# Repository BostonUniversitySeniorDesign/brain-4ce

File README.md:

<div style="text-align: center;">

# **Brain-4ce** - An EEG-based Brain-Computer Interface

</div>

<p align="center">
    
    <br>
    <em>Where thoughts become motion.</em>
</p>
<h2 style="text-decoration: underline; text-align: center">Designed by BU ECE 2023 Senior Design Capstone Team 4</h2>
<p align="center">
    
    <br>
    <em>From left to right: Brendan Shortall, Mitchell Gilmore, Dayanna De La Torres, Jonathan Mikalov, Alexander Johnson</em>
</p>
<br>

# Table of Contents
- [**Brain-4ce** - An EEG-based Brain-Computer Interface](#brain-4ce---an-eeg-based-brain-computer-interface)
- [Table of Contents](#table-of-contents)
- [Abstract](#abstract)
- [Getting Started](#getting-started)
- [Current State of the Project](#current-state-of-the-project)
- [Lessons Learned](#lessons-learned)
- [Bug Fixes](#bug-fixes)

<br>

# Abstract
The ability to manipulate objects using only your mind is no longer a far-fetched idea. While It may sound like something out of science fiction, our team has turned this into a reality. We have created a headset that utilizes electroencephalogram (EEG) technology to quickly and accurately record a user's neural activity. Our state-of-the-art deep learning algorithm then decodes these signals into predefined motor-imagery tasks.

This breakthrough technology is integrated with a computer game that provides the user with an environment to navigate using their mind. With the Brain-4ce (pronounced "Brain Force") headset, users can perform four different actions: rotating clockwise, rotating counterclockwise, moving forward, and moving backward. Each action corresponds to a physical motion that the user imagines themselves doing.

Our team was inspired to develop this project by our aspiration to bridge the digital divide for those who are physically disabled. With the Brain-4ce headset, users will be able to operate a computer, a wheelchair, and virtually anything else using nothing but their thoughts! The possibilities are endless, and we are excited to see what the future holds.
<br></br>

# Getting Started
- Please refer to our [Hardware Setup Guide](./hardware/README_HARDWARE.md) for instructions on setting up the hardware.
- Please refer to our [Software Setup Guide](./mainmenu/README_SOFTWARE.md) for instructions on setting up the software.
<br></br>

# Current State of the Project
As it currently stands, our project has three major components:
1. A working [EEG data capture headset](./hardware/electrical/cyton%20wired/) that interfaces with a [Python application](./GUI/) to monitor and record brain activity in real time.
2. A [convolutional neural network machine learning algorithm](./Physionet%20Dataloader/), trained on the recorded brain activity, for classifying motor-imagery tasks observed from a user wearing the headset.
3. [2D](./2D%20Game/) and [3D](./Virtual%20Environment/) video games developed in Python to demonstrate the efficacy of the neural network's brain activity classification.

The software communicates in real time using socket programming techniques to achieve parallelism and multithreading.
<br></br>

# Lessons Learned
- Developing on Apple Silicon, and ARM-based processors in general, is tricky for this project. Certain libraries, such as the [ChipKIT Core library](https://chipkit.net/wiki/index.php?title=ChipKIT_core) for compiling firmware onto the microcontroller, lack proper support for ARM architecture. We recommend performing all software development on an x64-based Windows machine. Some development is possible on Intel-based macOS and Linux, but it will probably save you a lot of headache to stick to Windows if possible.
- The microcontroller appears to have USB functionality built-in, which might make the USB to UART conversion unnecessary. This may be something to examine in [the documentation](https://ww1.microchip.com/downloads/en/DeviceDoc/PIC32MX1XX2XX%20283644-PIN_Datasheet_DS60001168L.pdf) during a future continuation of this project.
- The ADS1299 chip from Texas Instruments remains [difficult to obtain](https://www.findchips.com/search/ADS1299) as of Q2 2023 due to the ongoing chip shortage. We tried using the ADS1296 chip in its place, but this was unsuccessful because of differing startup and common-mode rejection configurations between the chips.
- If future boards are manufactured, it may be worth considering [paying for them to be machine-assembled](https://jlcpcb.com/parts). Assembling the boards by hand takes a long time and requires a substantial amount of electrical rules checking to ensure no shorts or incontinuity between components.
- Obtaining good skin contact for all electrodes is crucial to ensure proper reading of brain activity.
- The [OpenBCI Forum](https://openbci.com/forum/index.php?p=/discussions) is a great place to turn to for help troubleshooting. As is [their documentation](https://docs.openbci.com).
<br></br>

# Bug Fixes
- [Incorrect start byte configuration](https://github.com/atjohnson/brain-4ce-old/issues/10) - fixes an issue where the data stream is incorrectly formatted because the obsolete RFduino did some packet changing which no longer happens due to our wired USB connection.
- [Enable OpenBCI GUI to work with USB to UART controller](https://github.com/atjohnson/brain-4ce-old/issues/11) - fixes an issue where OpenBCI's GUI is unable to detect the Cyton board due to an ID mismatch with the USB to UART bridge IC.
- [Set up chipKIT Core library to work on local machine](https://github.com/atjohnson/brain-4ce-old/issues/12) - fixes an issue where Arduino IDE is unable to compile the firmware because it cannot locate the PIC32 compiler applications.
- [RXT and TXT LEDs not flashing](https://github.com/BostonUniversitySeniorDesign/brain-4ce/issues/4) - fixes an issue where the RXT and TXT LEDs on the board indicating data transmission over UART do not flash because the USB to UART bridge's firmware is configured improperly.

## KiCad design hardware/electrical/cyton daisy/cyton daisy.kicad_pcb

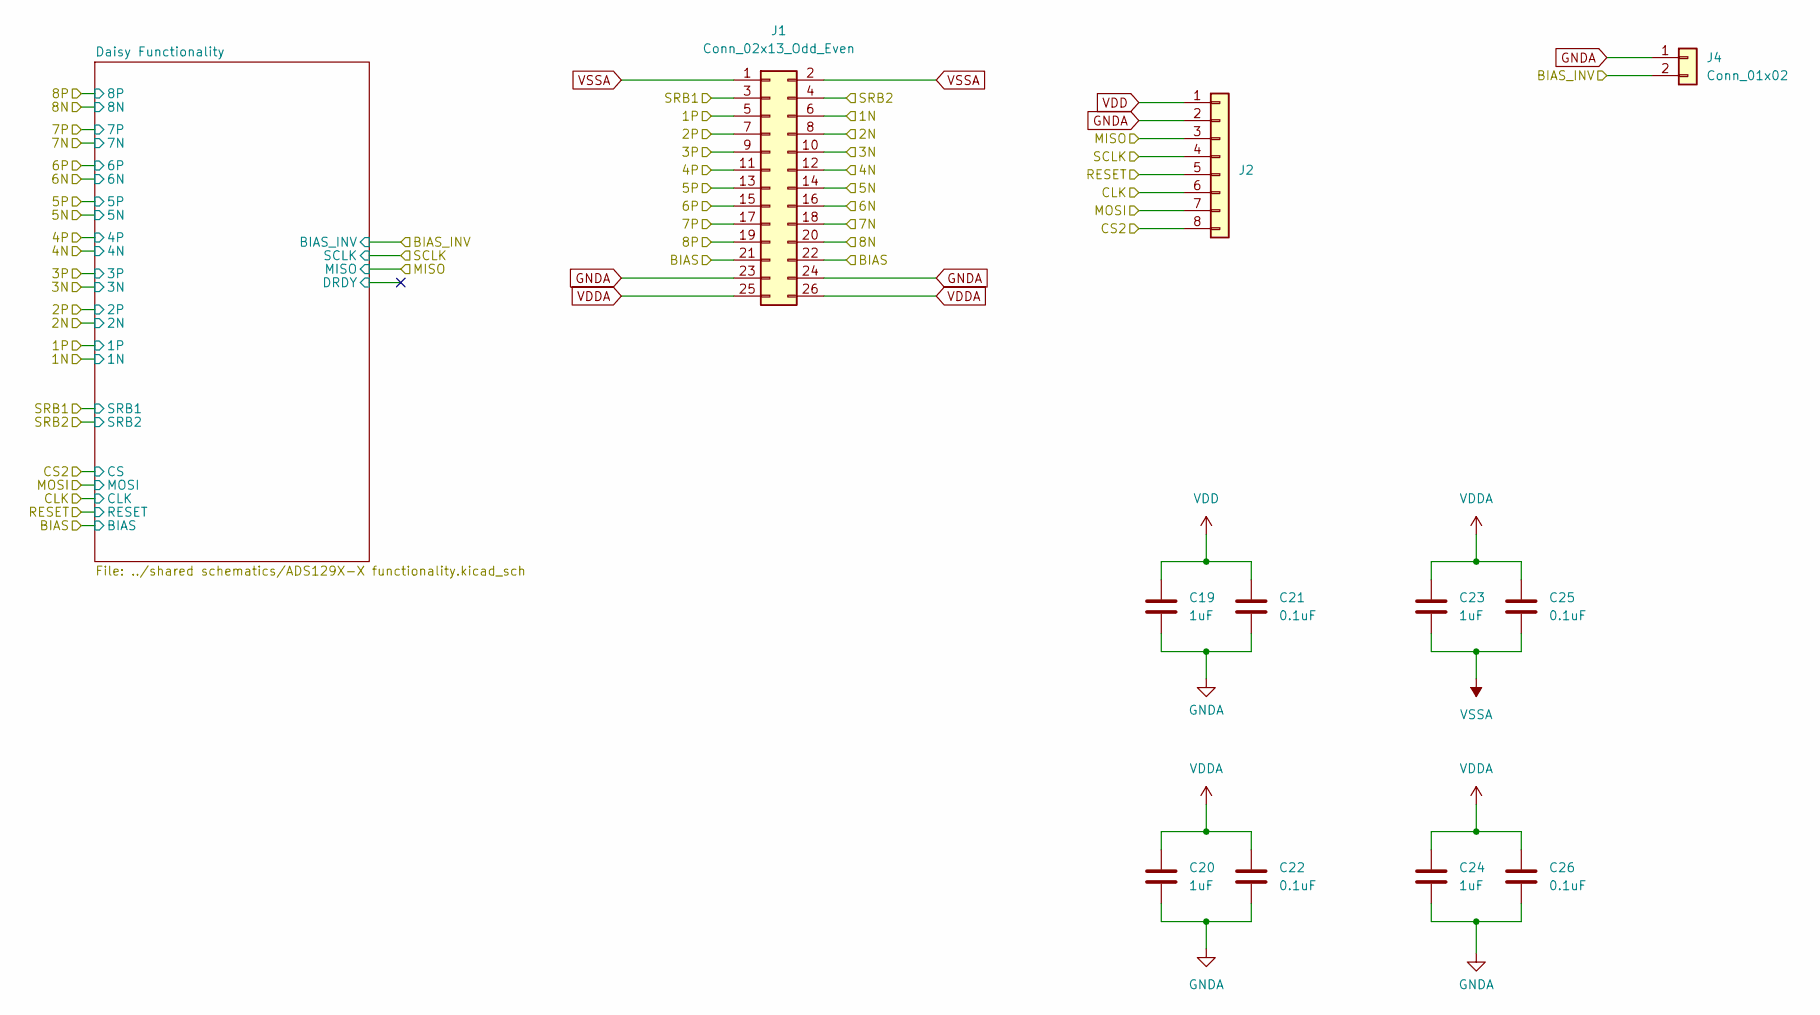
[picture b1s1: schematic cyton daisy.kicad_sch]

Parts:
C19, C20, C23, C24: 1uF; C_0402_1005Metric
C21, C22, C25, C26: 0.1uF; C_0402_1005Metric
J1: Conn_02x13_Odd_Even; PinHeader_2x13_P2.54mm_Horizontal
J2: Conn_01x08; PinSocket_1x08_P2.54mm_Vertical
J4: Conn_01x02; PinSocket_1x02_P2.54mm_Vertical

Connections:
/1N: J1.6; also elsewhere on the board
/1P: J1.5; also elsewhere on the board
/2N: J1.8; also elsewhere on the board
/2P: J1.7; also elsewhere on the board
/3N: J1.10; also elsewhere on the board
/3P: J1.9; also elsewhere on the board
/4N: J1.12; also elsewhere on the board
/4P: J1.11; also elsewhere on the board
/5N: J1.14; also elsewhere on the board
/5P: J1.13; also elsewhere on the board
/6N: J1.16; also elsewhere on the board
/6P: J1.15; also elsewhere on the board
/7N: J1.18; also elsewhere on the board
/7P: J1.17; also elsewhere on the board
/8N: J1.20; also elsewhere on the board
/8P: J1.19; also elsewhere on the board
/BIAS: J1.21, J1.22; also elsewhere on the board
/BIAS_INV: J4.2; also elsewhere on the board
/CLK: J2.6; also elsewhere on the board
/CS2: J2.8; also elsewhere on the board
/MISO: J2.3; also elsewhere on the board
/MOSI: J2.7; also elsewhere on the board
/RESET: J2.5; also elsewhere on the board
/SCLK: J2.4; also elsewhere on the board
/SRB1: J1.3; also elsewhere on the board
/SRB2: J1.4; also elsewhere on the board
GNDA: C19.2, C20.2, C21.2, C22.2, C24.2, C26.2, J1.23, J1.24, J2.2, J4.1; also elsewhere on the board
VDD: C19.1, C21.1, J2.1; also elsewhere on the board
VDDA: C20.1, C22.1, C23.1, C24.1, C25.1, C26.1, J1.25, J1.26; also elsewhere on the board
VSSA: C23.2, C25.2, J1.1, J1.2; also elsewhere on the board

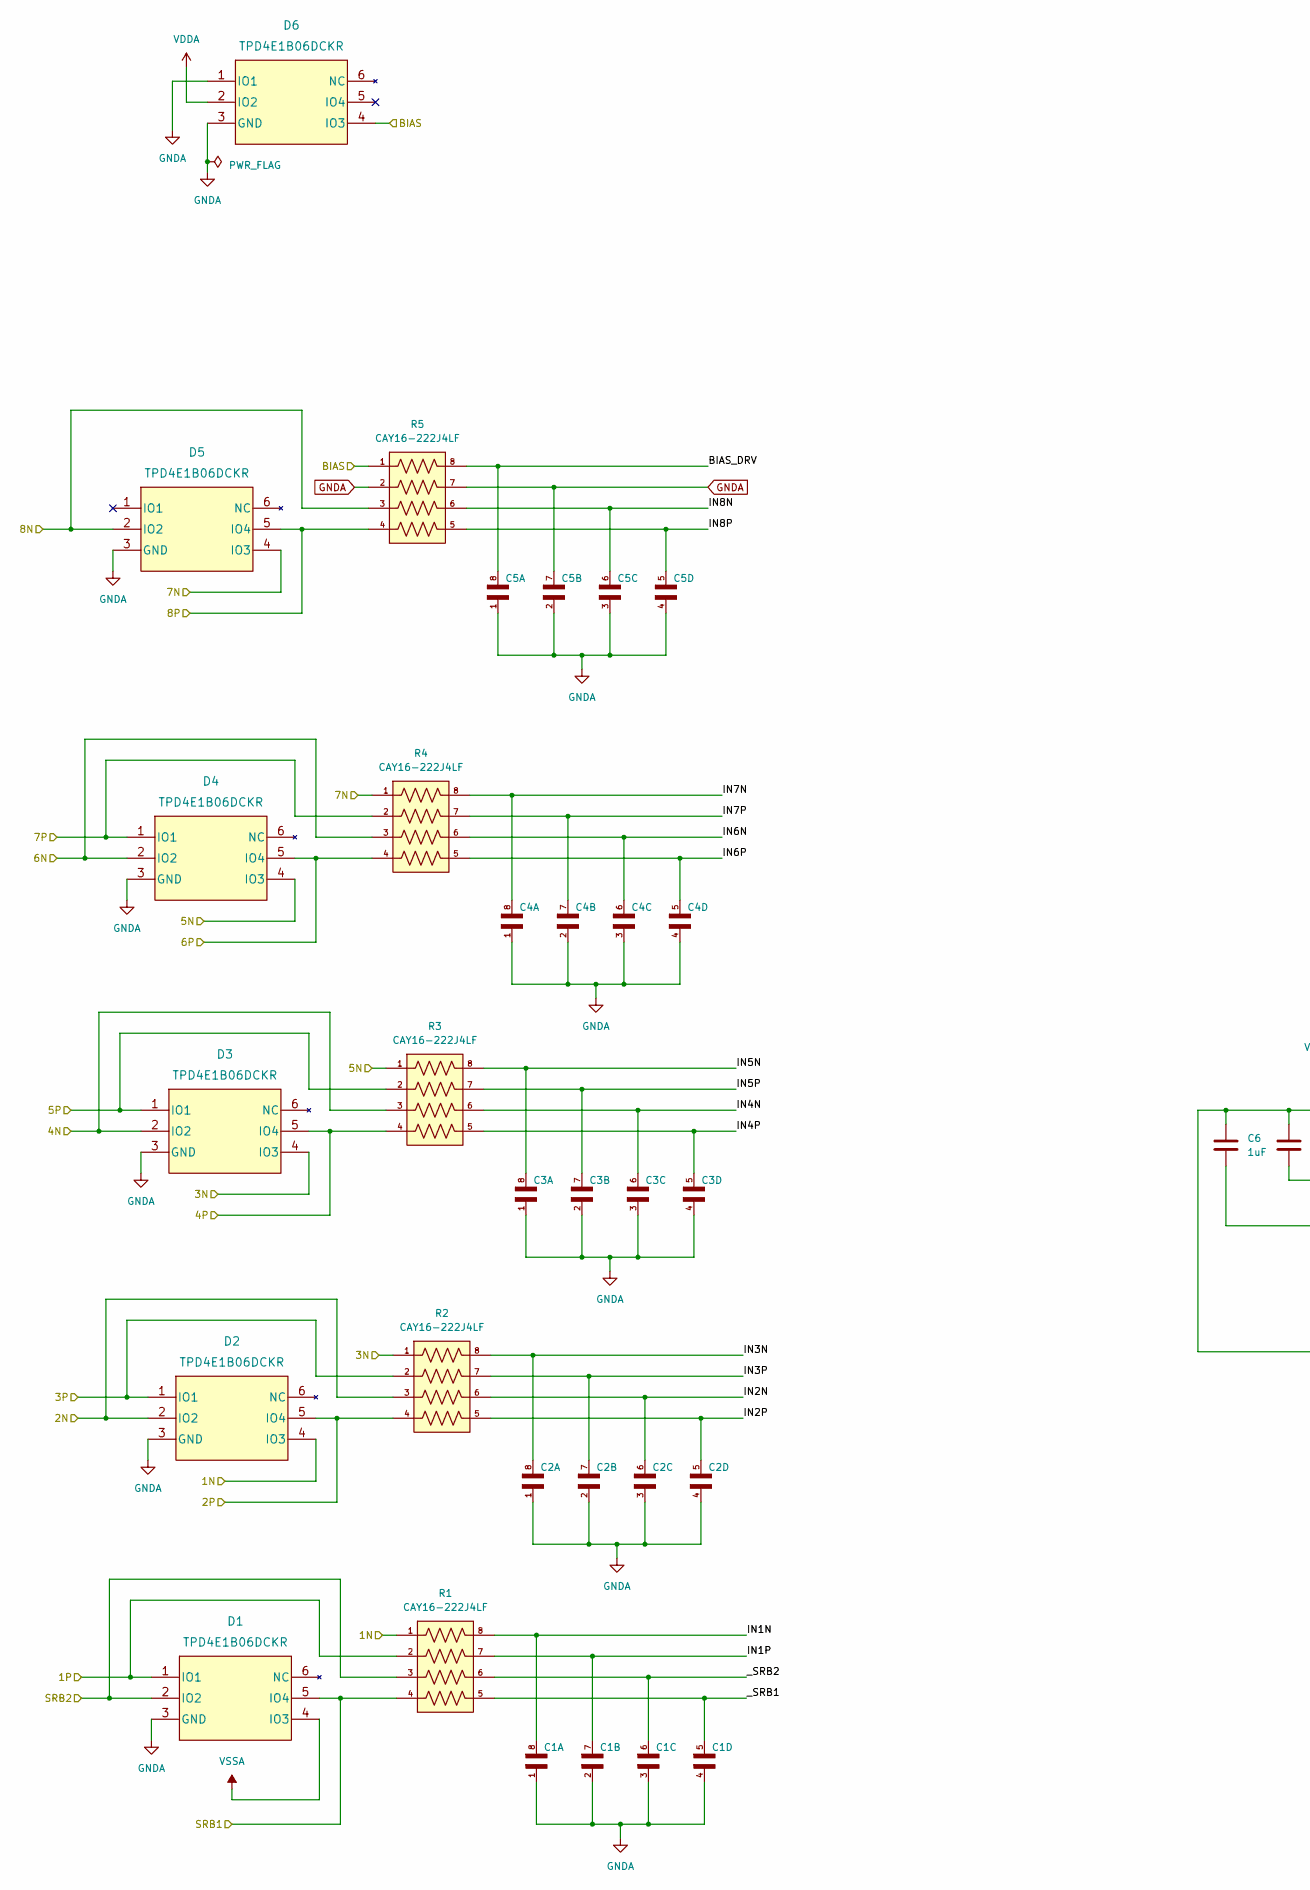
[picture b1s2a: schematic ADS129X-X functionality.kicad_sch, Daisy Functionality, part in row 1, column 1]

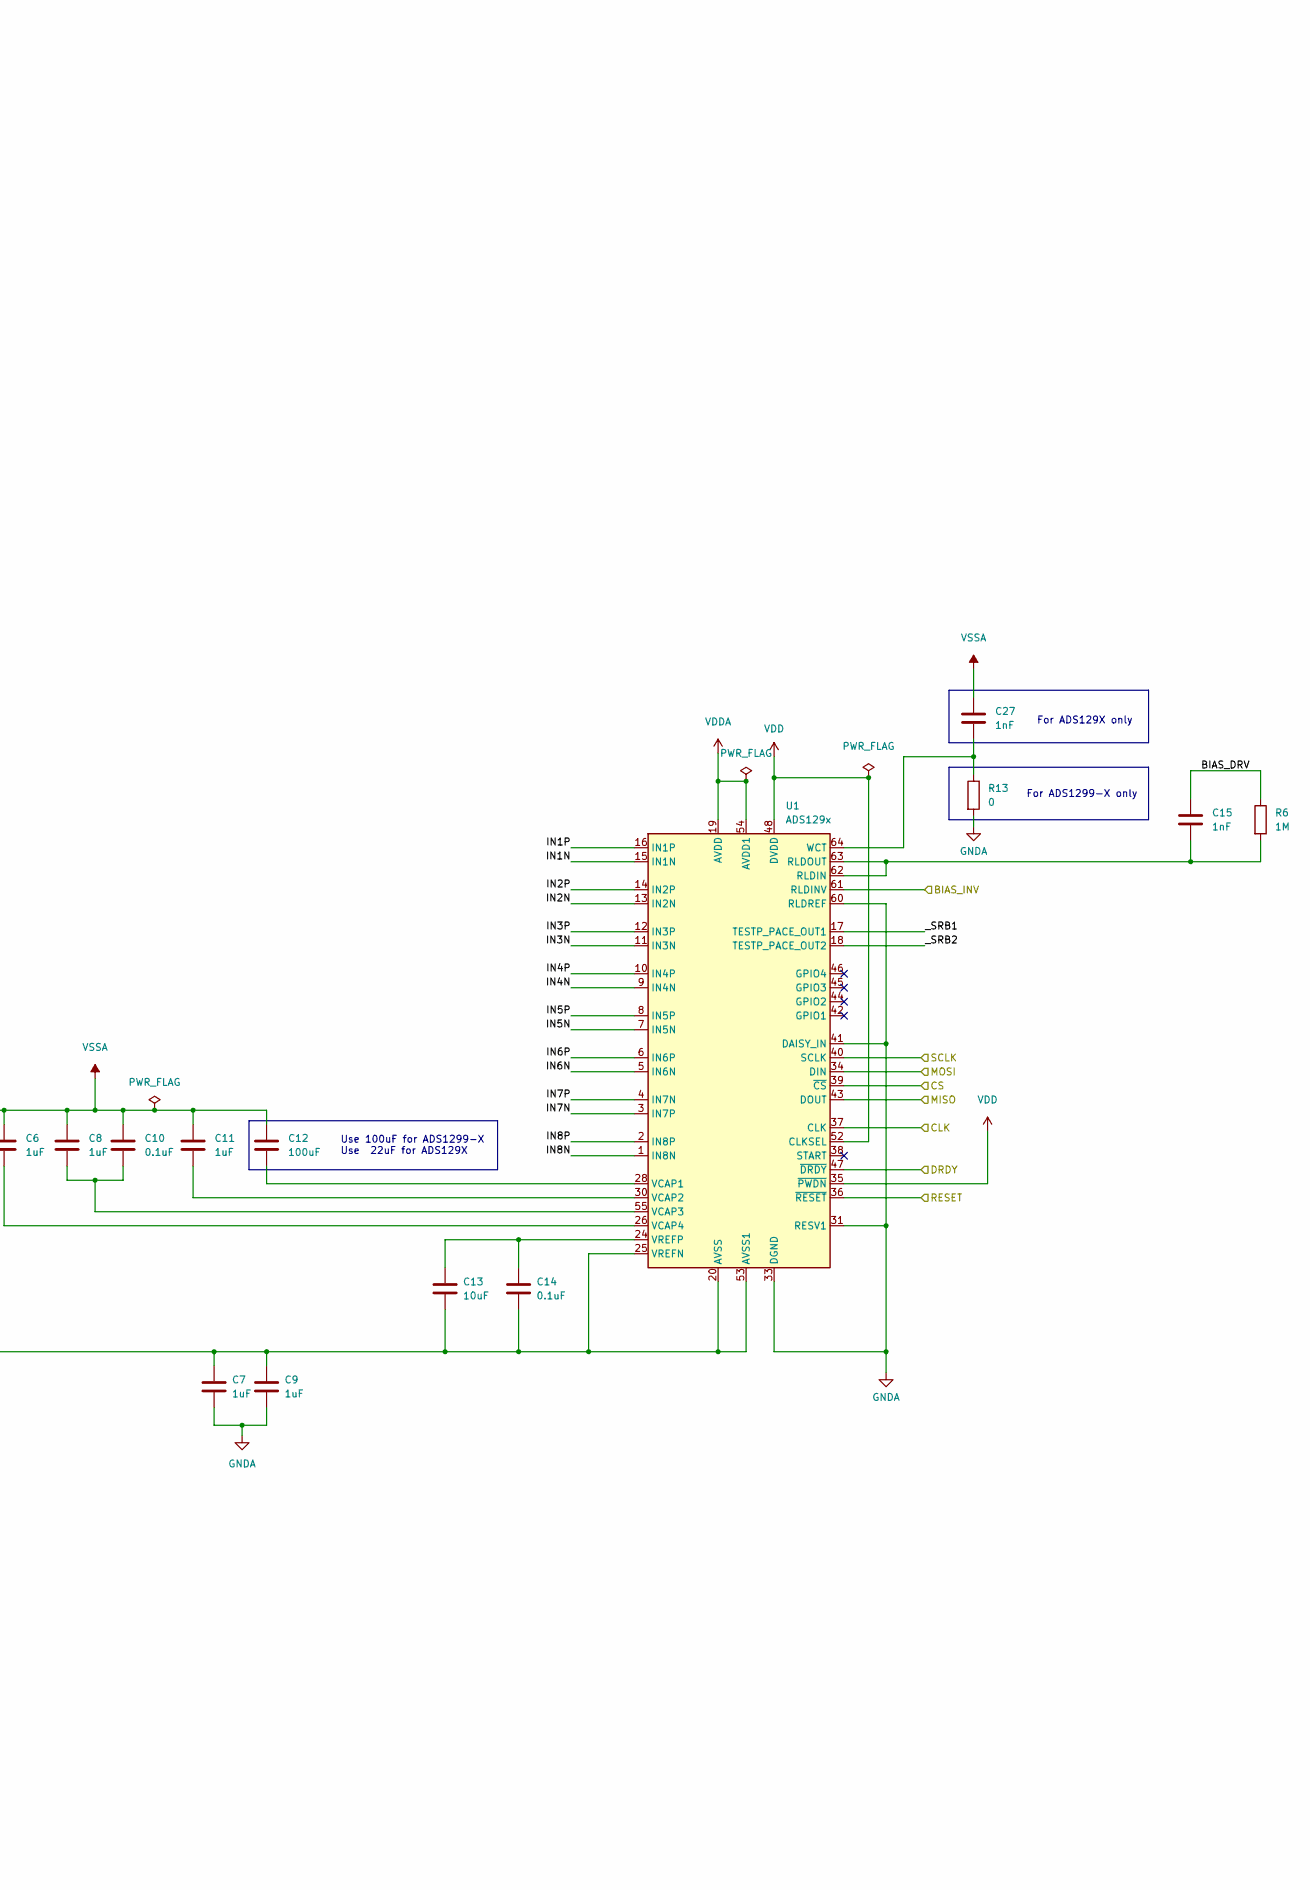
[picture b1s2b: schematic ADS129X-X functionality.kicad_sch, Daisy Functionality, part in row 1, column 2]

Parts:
C1, C2, C3, C4, C5: CA0508KRX7R9BB102; CAPCAXE50P210X130X94-8N
C6, C7, C8, C9, C11: 1uF; C_0402_1005Metric
C10, C14: 0.1uF; C_0402_1005Metric
C12: 100uF; C_1206_3216Metric
C13: 10uF; C_0603_1608Metric
C15, C27: 1nF; C_0402_1005Metric
D1, D2, D3, D4, D5, D6: TPD4E1B06DCKR
R1, R2, R3, R4, R5: CAY16-222J4LF; RESCAF80P320X160X60-8N
R6: 1M; R_0402_1005Metric
R13: 0; R_0402_1005Metric
U1: ADS129x; TQFP-64_10x10mm_P0.5mm

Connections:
/1N: D2.4 (IO3), R1.1; also elsewhere on the board
/1P: D1.1 (IO1), R1.2; also elsewhere on the board
/2N: D2.2 (IO2), R2.3; also elsewhere on the board
/2P: D2.5 (IO4), R2.4; also elsewhere on the board
/3N: D3.4 (IO3), R2.1; also elsewhere on the board
/3P: D2.1 (IO1), R2.2; also elsewhere on the board
/4N: D3.2 (IO2), R3.3; also elsewhere on the board
/4P: D3.5 (IO4), R3.4; also elsewhere on the board
/5N: D4.4 (IO3), R3.1; also elsewhere on the board
/5P: D3.1 (IO1), R3.2; also elsewhere on the board
/6N: D4.2 (IO2), R4.3; also elsewhere on the board
/6P: D4.5 (IO4), R4.4; also elsewhere on the board
/7N: D5.4 (IO3), R4.1; also elsewhere on the board
/7P: D4.1 (IO1), R4.2; also elsewhere on the board
/8N: D5.2 (IO2), R5.3; also elsewhere on the board
/8P: D5.5 (IO4), R5.4; also elsewhere on the board
/BIAS: D6.4 (IO3), R5.1; also elsewhere on the board
/BIAS_INV: U1.61 (RLDINV); also elsewhere on the board
/CLK: U1.37 (CLK); also elsewhere on the board
/CS2: U1.39 (~CS); also elsewhere on the board
/Daisy Functionality/BIAS_DRV: C5.8, C15.1, R5.8, R6.1
/Daisy Functionality/DRDY: U1.47 (~DRDY)
/Daisy Functionality/IN1N: C1.8, R1.8, U1.15 (IN1N)
/Daisy Functionality/IN1P: C1.7, R1.7, U1.16 (IN1P)
/Daisy Functionality/IN2N: C2.6, R2.6, U1.13 (IN2N)
/Daisy Functionality/IN2P: C2.5, R2.5, U1.14 (IN2P)
/Daisy Functionality/IN3N: C2.8, R2.8, U1.11 (IN3N)
/Daisy Functionality/IN3P: C2.7, R2.7, U1.12 (IN3P)
/Daisy Functionality/IN4N: C3.6, R3.6, U1.9 (IN4N)
/Daisy Functionality/IN4P: C3.5, R3.5, U1.10 (IN4P)
/Daisy Functionality/IN5N: C3.8, R3.8, U1.7 (IN5N)
/Daisy Functionality/IN5P: C3.7, R3.7, U1.8 (IN5P)
/Daisy Functionality/IN6N: C4.6, R4.6, U1.5 (IN6N)
/Daisy Functionality/IN6P: C4.5, R4.5, U1.6 (IN6P)
/Daisy Functionality/IN7N: C4.8, R4.8, U1.3 (IN7P)
/Daisy Functionality/IN7P: C4.7, R4.7, U1.4 (IN7N)
/Daisy Functionality/IN8N: C5.6, R5.6, U1.1 (IN8N)
/Daisy Functionality/IN8P: C5.5, R5.5, U1.2 (IN8P)
/Daisy Functionality/_SRB1: C1.5, R1.5, U1.17 (TESTP_PACE_OUT1)
/Daisy Functionality/_SRB2: C1.6, R1.6, U1.18 (TESTP_PACE_OUT2)
/MISO: U1.43 (DOUT); also elsewhere on the board
/MOSI: U1.34 (DIN); also elsewhere on the board
/RESET: U1.36 (~RESET); also elsewhere on the board
/SCLK: U1.40 (SCLK); also elsewhere on the board
/SRB1: D1.5 (IO4), R1.4; also elsewhere on the board
/SRB2: D1.2 (IO2), R1.3; also elsewhere on the board
GNDA: C1.1, C1.2, C1.3, C1.4, C2.1, C2.2, C2.3, C2.4, C3.1, C3.2, C3.3, C3.4, C4.1, C4.2, C4.3, C4.4, C5.1, C5.2, C5.3, C5.4, C5.7, C7.2, C9.2, D1.3 (GND), D2.3 (GND), D3.3 (GND), D4.3 (GND), D5.3 (GND), D6.1 (IO1), D6.3 (GND), R5.2, R5.7, R13.2, U1.31 (RESV1), U1.33 (DGND), U1.41 (DAISY_IN), U1.49 (DGND), U1.51 (DGND), U1.60 (RLDREF); also elsewhere on the board
unnamed: C15.2, R6.2, U1.62 (RLDIN), U1.63 (RLDOUT)
unnamed: C12.2, U1.28 (VCAP1)
unnamed: C11.2, U1.30 (VCAP2)
unnamed: C8.2, C10.2, U1.55 (VCAP3)
unnamed: C6.2, U1.26 (VCAP4)
unnamed: C13.1, C14.1, U1.24 (VREFP)
unnamed: C27.2, R13.1, U1.64 (WCT)
VDD: U1.35 (~PWDN), U1.48 (DVDD), U1.50 (DVDD), U1.52 (CLKSEL); also elsewhere on the board
VDDA: D6.2 (IO2), U1.19 (AVDD), U1.21 (AVDD), U1.22 (AVDD), U1.54 (AVDD1), U1.56 (AVDD), U1.59 (AVDD); also elsewhere on the board
VSSA: C6.1, C7.1, C8.1, C9.1, C10.1, C11.1, C12.1, C13.2, C14.2, C27.1, D1.4 (IO3), U1.20 (AVSS), U1.23 (AVSS), U1.25 (VREFN), U1.32 (AVSS), U1.53 (AVSS1), U1.57 (AVSS), U1.58 (AVSS); also elsewhere on the board

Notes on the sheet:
For ADS1299-X only
Use 100uF for ADS1299-X Use 22uF for ADS129X
For ADS129X only

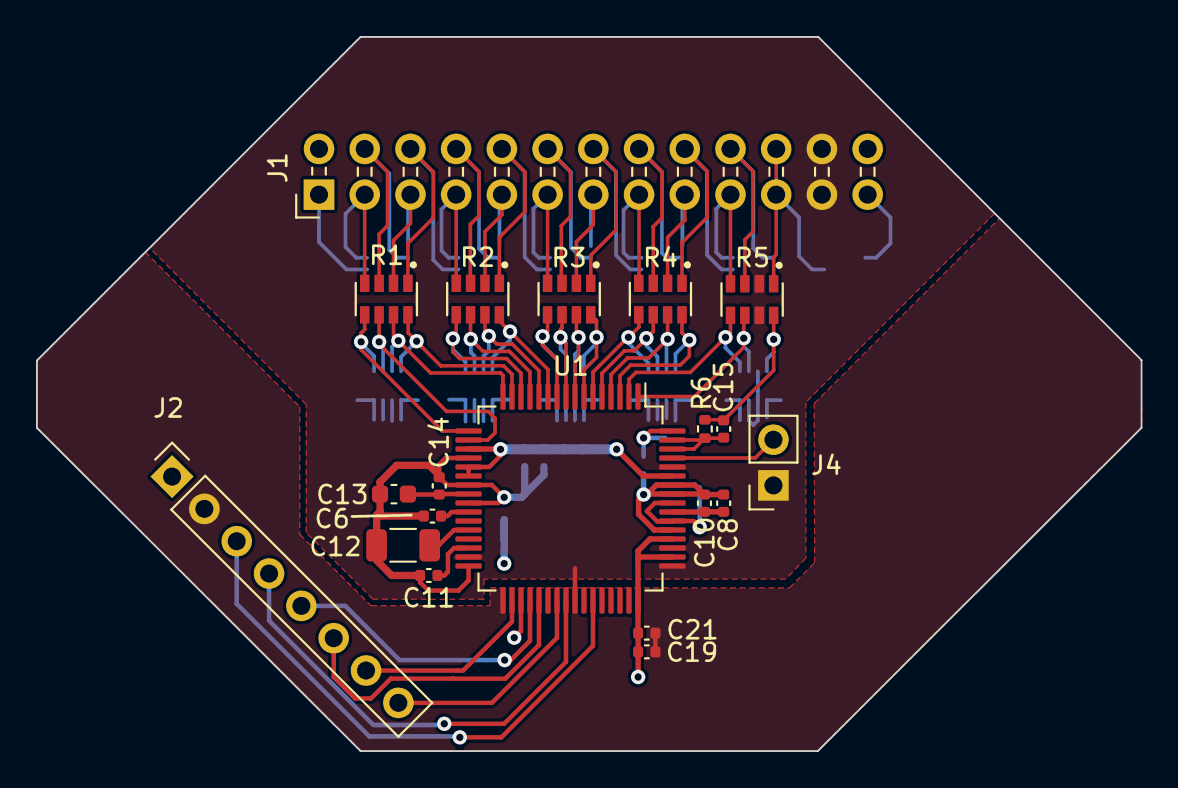
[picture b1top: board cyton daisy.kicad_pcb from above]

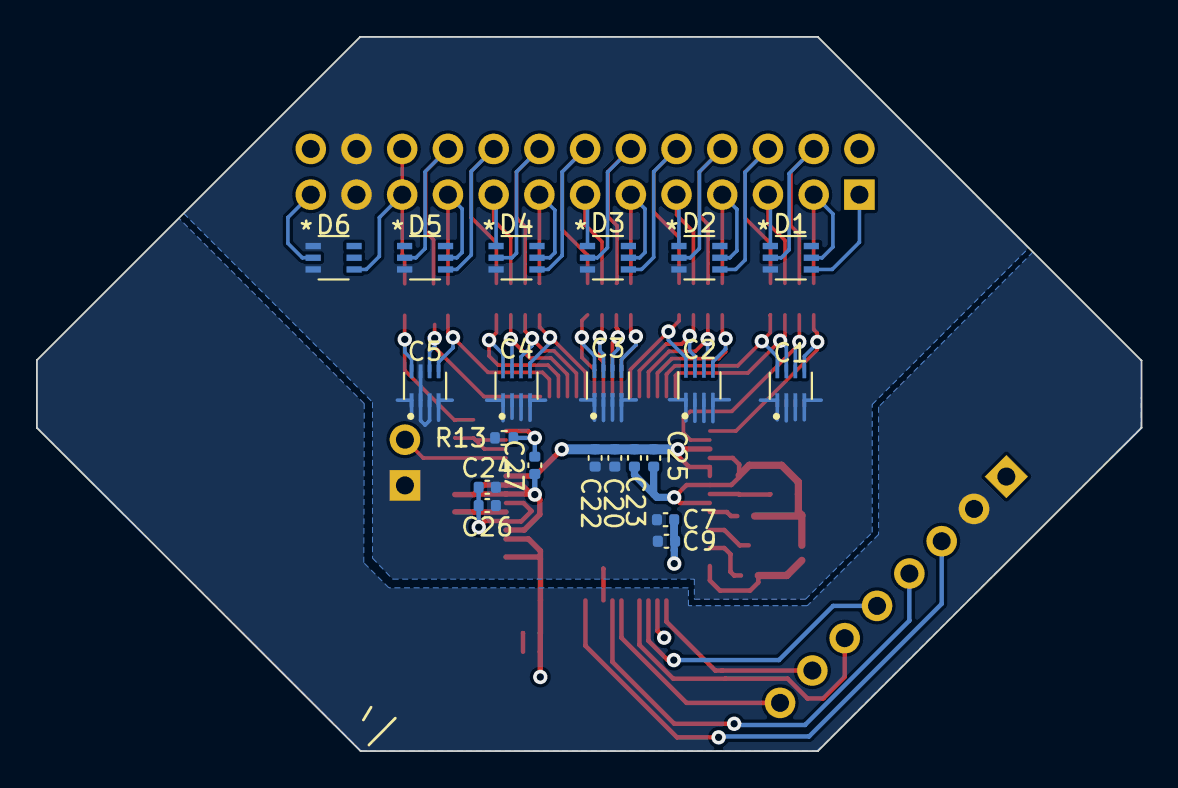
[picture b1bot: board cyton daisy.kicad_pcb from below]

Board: 4 copper layers, 61.4 x 39.7 mm, 41 parts (21 on the bottom side), 56 nets.

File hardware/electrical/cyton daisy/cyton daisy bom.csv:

"#","Reference","Qty","Value","Footprint","DNP"
"1","C1, C2, C3, C4, C5","5","CA0508KRX7R9BB102","Capacitor Arrays:CAPCAXE50P210X130X94-8N",""
"2","C6, C7, C8, C9, C11, C19, C20, C23, C24","9","1uF","Capacitor_SMD:C_0402_1005Metric",""
"3","C10, C14, C21, C22, C25, C26","6","0.1uF","Capacitor_SMD:C_0402_1005Metric",""
"4","C12","1","100uF","Capacitor_SMD:C_1206_3216Metric",""
"5","C13","1","10uF","Capacitor_SMD:C_0603_1608Metric",""
"6","C15, C27","2","1nF","Capacitor_SMD:C_0402_1005Metric",""
"7","D1, D2, D3, D4, D5, D6","6","TPD4E1B06DCKR","TSV - Diodes:TPD4E1B06DCKR",""
"8","J1","1","Conn_02x13_Odd_Even","Connector_PinHeader_2.54mm:PinHeader_2x13_P2.54mm_Horizontal",""
"9","J2","1","Conn_01x08","Connector_PinSocket_2.54mm:PinSocket_1x08_P2.54mm_Vertical",""
"10","J4","1","Conn_01x02","Connector_PinSocket_2.54mm:PinSocket_1x02_P2.54mm_Vertical",""
"11","R1, R2, R3, R4, R5","5","CAY16-222J4LF","Resistor Arrays:RESCAF80P320X160X60-8N",""
"12","R6","1","1M","Resistor_SMD:R_0402_1005Metric",""
"13","R13","1","0","Resistor_SMD:R_0402_1005Metric",""
"14","U1","1","ADS129x","Package_QFP:TQFP-64_10x10mm_P0.5mm",""

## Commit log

2022-11-20 Initializing readme file
2022-11-20 Fixing typos
2022-12-04 added 3d sphere and plane
2022-12-07 control camera pos on 'a'
2022-12-08 move sphere in 4 directions
2022-12-09 barrier, change plane color
2022-12-09 uncomment
2023-01-09 project snapshot
2023-01-10 finished layout
2023-01-11 moved via that missed VSSA plane
2023-01-12 fixed D9 footprint problem
2023-01-22 updated gerbers
2023-01-23 Create Links
2023-01-23 First Semester Report 2022
2023-01-23 Create First Semester Report 2022
2023-01-23 Create temp
2023-01-23 Shark Tank
2023-01-24 Progress Update Video
2023-01-24 PDRR
2023-01-24 PDR Room Presentation
2023-01-24 Team Agreement
2023-01-24 IDRs Sem 1
2023-01-24 Financials
2023-01-24 Project Proposal
2023-01-24 GANTT CHART
2023-01-24 PDRR Report
2023-01-31 change barrier size
2023-02-01 tentative camera angle changes
2023-02-07 new generate library for functions
2023-02-07 fix lighting
2023-02-17 sphObject now goes opposite direction of camera
2023-02-17 CAMERA ORIENTATION FIXED!
2023-02-17 fix sphObject shading
2023-02-20 move backwards
2023-02-22 add new testing feature that automatically turns sphere
2023-03-02 uncomment simulation
2023-03-04 restructured hardware files
2023-03-04 Added HW support for ADS129X
2023-03-04 added power supply
2023-03-05 snapshot of current MCU work
2023-03-06 added firmware file
2023-03-06 added test function to read channels
2023-03-06 finished layout working on silkscreen
2023-03-06 fixed silk and generated fab outputs
2023-03-06 renamed ADC schmatic for generatlity
2023-03-06 daisy design that support new ADC
2023-03-07 changed C27 from an 0402 package to a 0201 package
2023-03-23 add gui
2023-03-23 add venv
2023-03-23 remove dir
2023-03-25 fixed RX and TX pins configuration
2023-03-25 added RX and TX silkscreen
2023-03-27 color loop WIP
2023-03-27 enlarged mounting holes
2023-03-27 removed silk from mounting holes
2023-03-27 restructured hardware folder and added OpenBCI_GUI patch/documentation
2023-03-28 firmware documentation
2023-03-31 initial work on interfacing with the EEG
2023-03-31 added BrainFlow initiialization
2023-03-31 small changes
2023-03-31 adding arg parsing
2023-04-01 add brainflow code
2023-04-01 add stl and CAD drawings
2023-04-01 add gcode
2023-04-01 Socket programs to transfer data line by line
2023-04-02 fix code organization, remove redundancies
2023-04-02 loop colors between tasks
2023-04-02 add text, 5s intervals
2023-04-02 add instruction
2023-04-02 add comments
2023-04-02 current snapshot
2023-04-03 modify for classes/objects
2023-04-03 Converted the args to a dicionary to pass arguments as keyword arguments
2023-04-03 Improved OOP for the CytonBoard class with a lazy computational model
2023-04-03 remove extra class
2023-04-03 add physionet data loader
2023-04-03 fix mistake
2023-04-05 Remove 0 index
2023-04-05 add Channel Placement jpeg
2023-04-05 add fake ML
2023-04-05 Attempt to generalize sockets
    This code is attempting to receive data directly from the python CLI program that simulates board data
2023-04-05 Attempt to generalize sockets
    This code makes attempts to grab the data from the CLI program that simulates board data
2023-04-06 Fixed errors
2023-04-06 change delays, remove circles
2023-04-06 add server socket programming into venv
2023-04-11 Fix annoying camera issue
2023-04-11 Implement new test texture
2023-04-11 Remove redundant code
2023-04-11 add blender file
2023-04-11 new plane background
2023-04-11 add caseV3.stl
2023-04-12 add new star shape from blender
2023-04-12 replace star texture
2023-04-12 add stars in-game, move text
2023-04-12 new control features for smooth transitioning
2023-04-12 Fix jagged camera issue
2023-04-13 Brain
2023-04-13 add brain
2023-04-13 Restore to prev version
2023-04-13 Fix brain angle issue
2023-04-13 Fix lighting hpr
2023-04-13 new star texture
2023-04-13 change background color
2023-04-13 add score and collision detection
2023-04-13 Fix collision detection
2023-04-13 reconfigure networking directions
2023-04-13 remove print
2023-04-17 Adding bootloader hex file and bootloader instructions to README
2023-04-18 Rotate stars in place
2023-04-18 remove comments
2023-04-18 fix crash
2023-04-18 fix crash by just ignoring it
2023-04-18 fix the crash completely
2023-04-18 Created Bare ML Model
    Intended for Brendan to build upon/ test with board. Will optimize for real-time data and sharing later.
2023-04-18 Rename Requirements.txt.txt to Requirements.txt
2023-04-20 change wording for clarity
2023-04-20 removed 'Unused File'
2023-04-20 "removed Brainflow"
2023-04-20 converted ipynb to py for better VC
2023-04-20 update hardware
2023-04-20 add arg parser to dataloader
2023-04-20 remove commented out code
2023-04-20 removing the commented code at the end of the file
2023-04-20 removed fakeml file
2023-04-22 add 2d game
2023-04-22 delete
2023-04-23 removed server_socket.py
2023-04-23 changed to assign port number based on CLI args
2023-04-23 adjust for any screen res
2023-04-24 network architecture and dataloader
2023-04-24 exception handling on escape
2023-04-24 round to 1 sigfig
2023-04-25 implement filter transform, begin trainer
2023-04-25 updated game flow logic
2023-04-25 develop trainer
2023-04-25 fix very significant bug, remove comments, delete extra files
2023-04-25 remove extra libs
2023-04-25 open save window after tasks finish
2023-04-25 add new venv
2023-04-26 finished trainer add argparse
2023-04-26 add requirements.txt
2023-04-26 remove test.py
2023-04-27 change box pos every x sec
2023-04-28 add countdown, final store, fix bug
2023-04-28 add 30s game
2023-04-28 delay by 0.5s for movement
2023-04-28 rename
2023-04-28 add boardstreamer functionality
2023-04-29 Add cyton
2023-04-30 add data
2023-04-30 remove
2023-04-30 add trained models + results
2023-04-30 Update README.md
    Adding the Engineering Addendum in addition to Markdown files for the Hardware and Software Reports.
2023-05-01 Adding Hardware Report
2023-05-01 Adding prototype testing plans and reports
2023-05-01 add imagery option
2023-05-01 add timestamps, change tasks
2023-05-01 save changes
2023-05-01 add resources
2023-05-02 store input into an array
2023-05-02 on close, export
2023-05-03 change model, add new results
2023-05-04 rm models and results
2023-05-04 remove debug config
2023-05-04 init menu
2023-05-04 find fix
2023-05-04 finish menu
2023-05-04 accept ints as input
2023-05-04 remove extra lines
2023-05-04 move readme to mainmenu
2023-05-05 update readme with new info
2023-05-05 fix link
2023-05-08 comment out

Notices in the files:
parts and their libraries:
Copyright 2021 Accelerated Designs. All rights reserved.
